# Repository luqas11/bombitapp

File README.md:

# bombitapp

### What is this
This project is a **device that controls and protects electric water pump systems**, built with an **ESP8266** based board, and operated from a mobile app developed in [React Native](https://reactnative.dev/). The device is able to preventively cut off power from the pump engines when an abnormal functioning is detected.

It's designed to operate over this preexisting pump setup:
- 2 220VAC 1/2 HP pumps.
- 2 water tanks.
- 2 water level sensors, placed inside the tanks and made by an on/off switch that turns on when the tank gets emptied and turns off when the filling process is complete. That switch operates directly at 220VAC and it's signal is plugged in to the pumps.
- 2 separated pipe circuits, each one connected to a different tank and pump. 

For different mechanical reasons, the sensors sometimes fail and keep the pumps engines running indefinitely, until manually fixed. If this happens, both the engines and the tanks could result **physically damaged** if the problem isn't solved quickly. This device's idea is to **cut pump power** if the sensor is sending the signal over a time period that exceeds some predefined threshold, to protect the setup. From a mobile app, the user can **resume the power after fixing the problem**, or **read the tank filling time history** to get an idea of the expected values. 

### Components
The project has the following components and features:

##### Hardware
- An ESP8266 based board, able to connect to the home Wi-Fi network.
- A custom PCB, to allow the ESP mounting and connection to the inputs and ouputs.
- 2 220VAC inputs, to recieve the tank water level signal. The ESP will read that signal to make it's decissions.
- 2 220VAC outputs, to power the water pumps. The ESP will power them with the water level sensor signal or not, depending on it's decissions.
- 1 5VCC input, to power the ESP board.
- 1 LED to indicate the WiFi connection status.

##### Firmware
- A sketch written in C++ and loaded to the ESP.
- Serves a webpage that allows the user to initially configure the WiFi credentials.
- Allows the level sensor signal to reach the output and power the pump until a time threshold is exceeded. After that, the connection is stopped to prevent the engine to keep working. If the signal stops before the threshold (i. e. the filling was successful), nothing happens.
- The time threshold can be setted via an HTTP request.
- Allows to resume the pump power via an HTTP request, overriding the stop state.
- The current engine working time can be get with an HTTP request.
- Allows to see the latest 10 engine run times via an HTTP request.
- Allows to see an average of all the previous engine run times via an HTTP request.
- The water level sensor status can be seen via an HTTP request (i. e. if it's on or off).

##### Mobile App
- A React Native mobile app compiled for Android.
- Gives a nice and human-friendly presentation layer for the firmware interaction, showing engine status and actions that can be made through HTTP.

### Screenshots
##### Mobile App

##### PCB 3D model

##### Circuit schematic

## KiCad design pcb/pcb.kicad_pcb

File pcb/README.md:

# PCB

This is a PCB design that implements the connections between the 220VAC relays and optocoupliers and the ESP board, along with all the necessary 3D printed parts to enable component mounting. The circuit schematic and the PCB layout are printed in the `pcb-schematic.pdf` and `pcb-layout.pdf` files respectively.

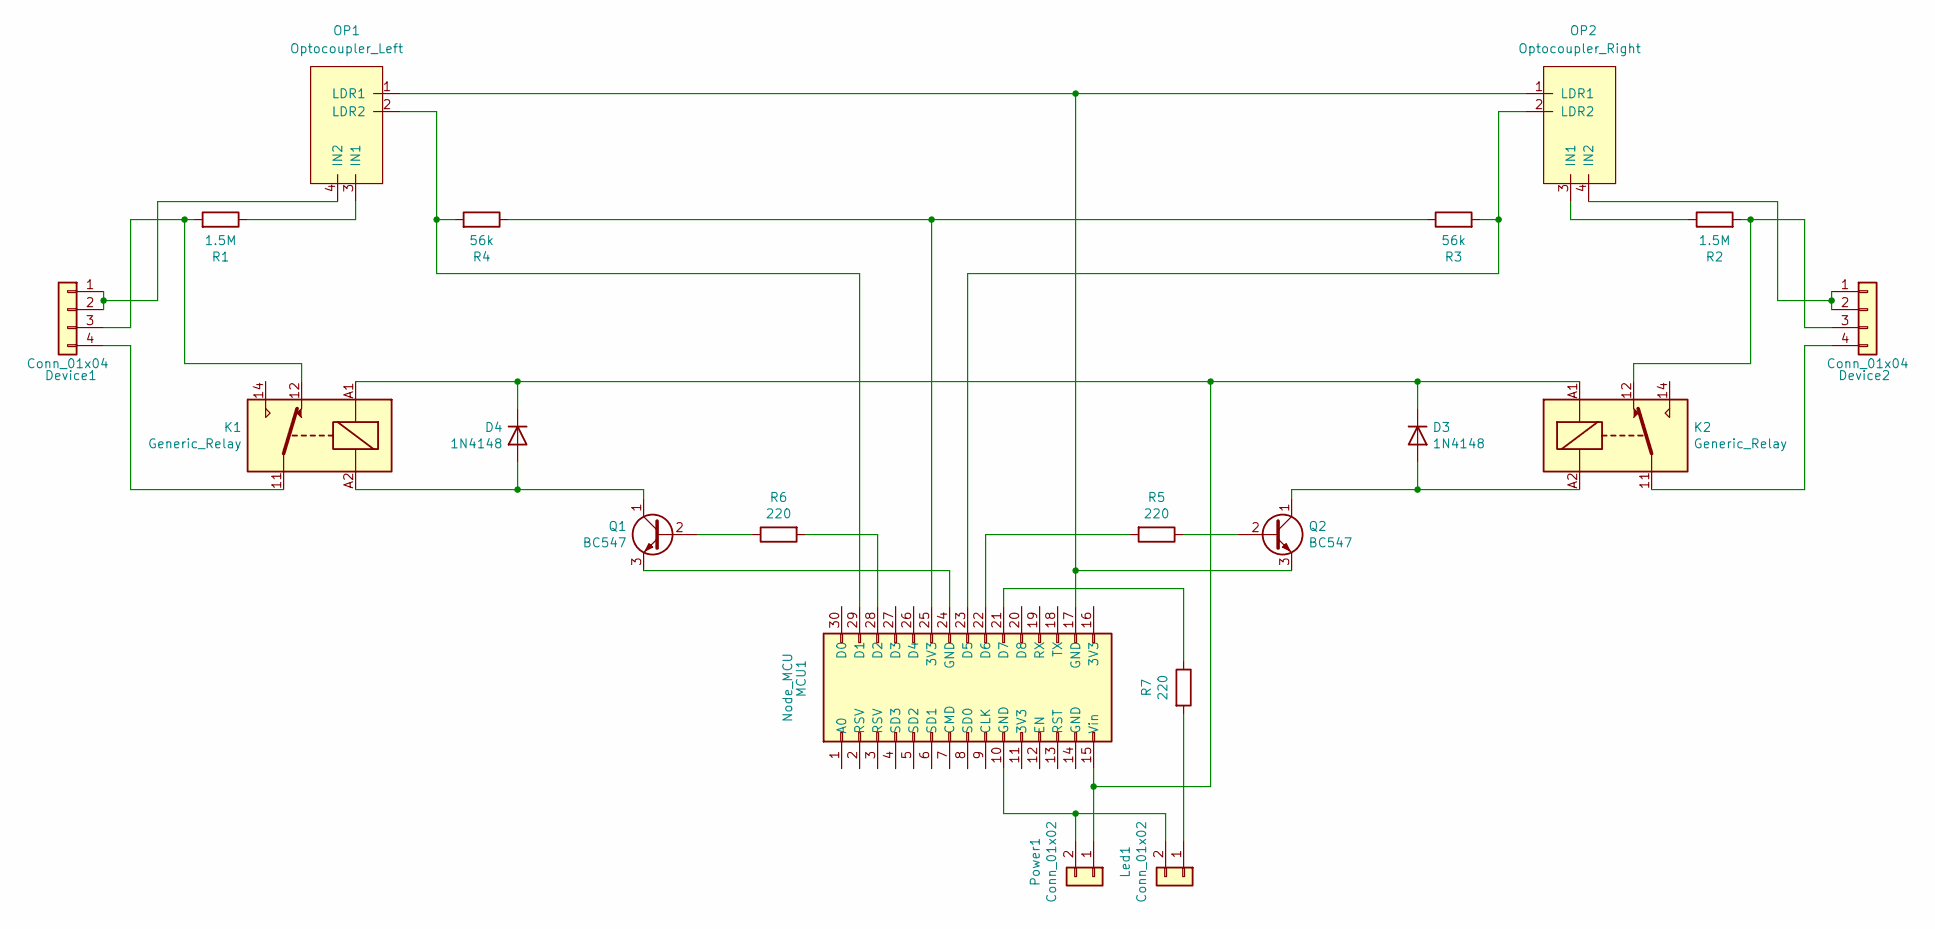
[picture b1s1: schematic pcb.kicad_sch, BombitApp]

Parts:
D3, D4: 1N4148; D_DO-35_SOD27_P7.62mm_Horizontal
Device1, Device2: Conn_01x04; TerminalBlock_1x04
K1, K2: Generic_Relay; Relay_SPDT_Finder_36.11
Led1: Conn_01x02; PinSocket_1x02
MCU1: Node_MCU
OP1: Optocoupler_Left
OP2: Optocoupler_Right
Power1: Conn_01x02; PinSocket_1x02
Q1, Q2: BC547; TO-92_Inline
R1, R2: 1.5M; R_Axial_DIN0207_L6.3mm_D2.5mm_P10.16mm_Horizontal
R3, R4: 56k; R_Axial_DIN0207_L6.3mm_D2.5mm_P10.16mm_Horizontal
R5, R6, R7: 220; R_Axial_DIN0207_L6.3mm_D2.5mm_P10.16mm_Horizontal

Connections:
unnamed: D3.2 (A), K2.A2, Q2.1 (C)
unnamed: D3.1 (K), D4.1 (K), K1.A1, K2.A1, MCU1.15 (Vin), Power1.1
unnamed: D4.2 (A), K1.A2, Q1.1 (C)
unnamed: Device1.1, Device1.2, OP1.4 (IN2)
unnamed: Device1.3, K1.12, R1.2
unnamed: Device1.4, K1.11
unnamed: Device2.1, Device2.2, OP2.4 (IN2)
unnamed: Device2.3, K2.12, R2.2
unnamed: Device2.4, K2.11
unnamed: Led1.1, R7.2
unnamed: Led1.2, MCU1.10 (GND), Power1.2
unnamed: MCU1.25 (3V3), R3.1, R4.1
unnamed: MCU1.29 (D1), OP1.2 (LDR2), R4.2
unnamed: MCU1.28 (D2), R6.2
unnamed: MCU1.23 (D5), OP2.2 (LDR2), R3.2
unnamed: MCU1.22 (D6), R5.2
unnamed: MCU1.21 (D7), R7.1
unnamed: OP1.3 (IN1), R1.1
unnamed: MCU1.17 (GND), OP1.1 (LDR1), OP2.1 (LDR1), Q2.3 (E)
unnamed: OP2.3 (IN1), R2.1
unnamed: Q1.2 (B), R6.1
unnamed: MCU1.24 (GND), Q1.3 (E)
unnamed: Q2.2 (B), R5.1

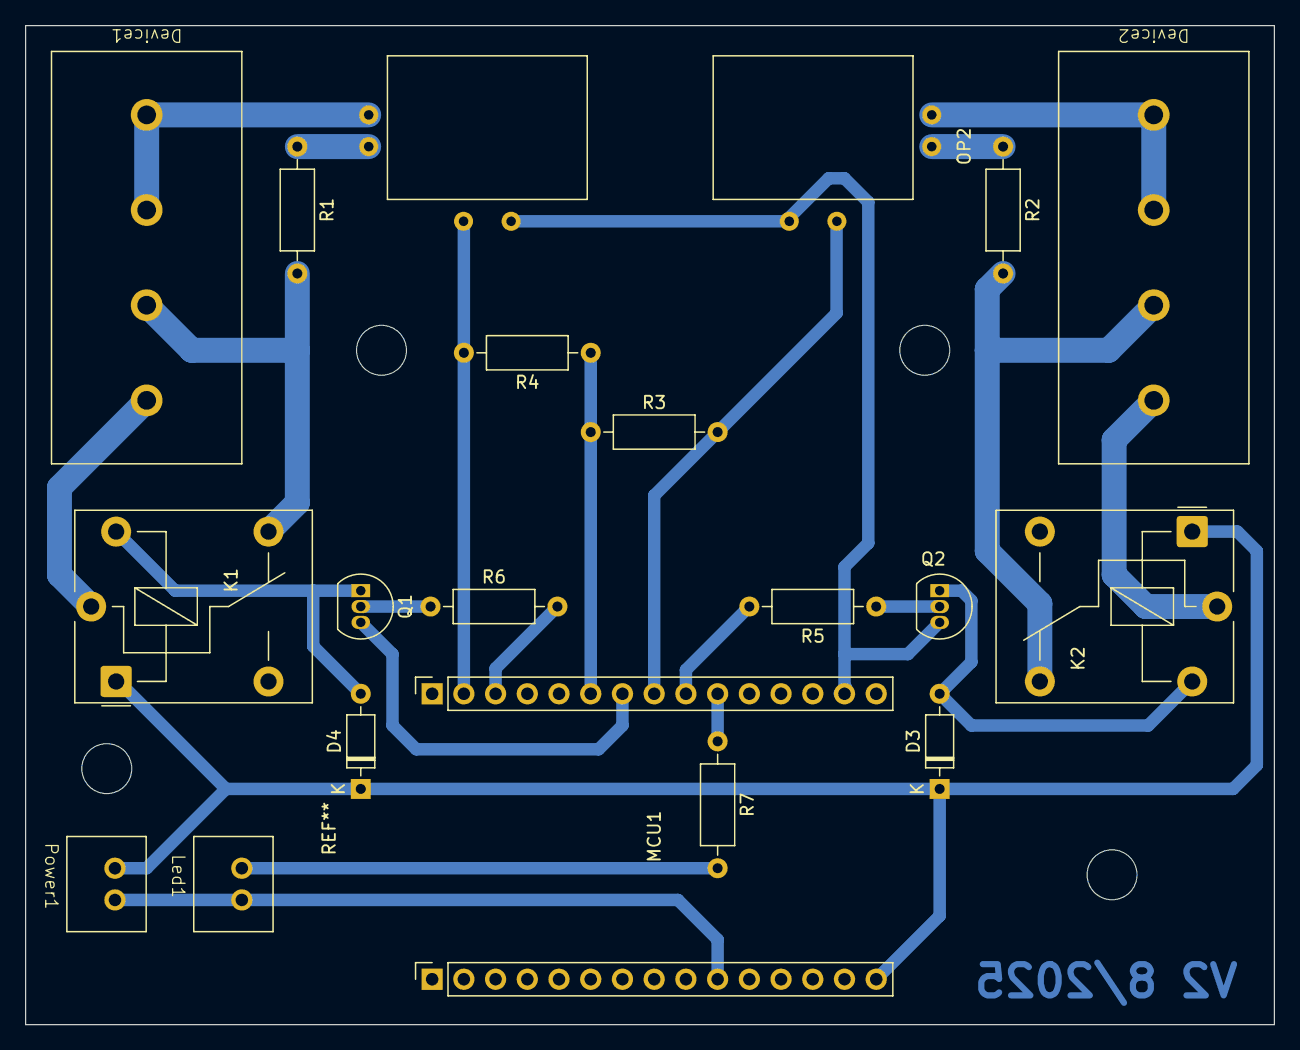
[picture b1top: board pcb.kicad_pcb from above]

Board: 2 copper layers, 100.0 x 80.0 mm, 20 parts (0 on the bottom side), 23 nets.

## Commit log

2023-05-14 Init React Native project
2023-05-14 Add postman collection
2023-05-14 Add VSCode workspace config
2023-05-14 Add json-server mock
2023-05-14 Update project version number
2023-05-14 Update Postman collection
2023-05-15 Change recommended linter
2023-05-17 Add UI desing references
2023-05-18 Add app icon and set app name
2023-05-18 Fix build error
2023-05-18 Update linter end of line configuration
2023-05-20 Add StatusCard and ButtonWithIcon components
2023-06-02 Add app navigation structure and JSDoc rules
2023-06-04 Add RequestStatusIndicator, ConfigCard, TimeLimitCard and VersionHistoryCard components and complete screens content
2023-06-04 Fix SettingsScreen visual error
2023-06-11 Add modal context and history modal implementation
2023-06-16 Add confirmation and information modals
2023-06-16 Refactor ModalContext to simplify code
2023-06-20 Add fetching logic and implement Zustand global state
2023-09-02 Relocate .vscode folder
2023-09-02 Set test context name
2023-09-02 Set context name to the correct one
2023-09-02 Configure project as a workspace
2023-09-10 Fix typo
2023-09-10 Add new sensor status indicator design
2023-09-10 Add sensor status indicator
2023-09-10 Add remaining services happy paths
2023-09-10 Add error handling to settings requests
2023-09-11 Implement name change logic to the settings screen
2023-09-11 Add loading animation design for the confirmation modal
2023-09-12 Add .env file to set environment specific variables
2023-09-12 Fix wrong time format
2023-09-12 Rename Postman files to match project name
2023-09-12 Add firmware project scaffolding
2023-09-14 Add endpoints structure and implement WiFi connection
2023-09-15 Add EEPROM management utilities
2023-09-15 Update comment
2023-09-15 Add JSON formatting utilities
2023-09-15 FIx comments format
2023-09-15 Implement Not found and status endpoints, and update Postman collection
2023-09-16 Add inputs and outputs status processing
2023-09-16 Implement history clear and limit change endpoint logic
2023-09-17 Implement input forced stop
2023-09-17 Implement EEPROM persitence to state variables
2023-09-17 Add status LED blink behaviour
2023-09-17 Fix bug reading history from memory
2023-09-17 Add LED indication for network status
2023-09-18 Remove internal pullup from inputs
2023-09-19 Refactor variable naming and update Postman collection
2023-09-19 Update comments
2023-09-19 Rename endpoint
2023-09-19 Update mock to match firmware changes
2023-09-19 Standardize variable naming across the project
2023-09-19 Update comments to match the project naming conventions
2023-09-20 Configure Android theme colors
2023-09-20 Reorder modal buttons
2023-09-20 Update files dates
2024-02-11 Add circuit and PCB design
2024-08-05 Add pcb directory to VSCode workspace
2024-08-06 Add new terminal block model and update PCB design
2024-08-08 Add pin socket model and update PCB
2024-12-20 Fix wrong output status logic
2024-12-20 Align footprints and PCB components placement
2024-12-20 Add PCB ground plane border clearance
2024-12-20 Add PCB layout and schematic PDFs
2024-12-22 Add new optocoupler model
2024-12-22 Update optocoupler footprint and PCB with new model
2024-12-22 Update schematic and layout PDFs
2024-12-23 Add power micro USB socket model
2024-12-25 Migrate firmware project from Arduino VSCode extension to IDE 2
2024-12-25 Upgrade React Native version from 0.71 to 0.76
2024-12-25 Remove RN template readme
2024-12-25 Add PCB mounting holes
2024-12-25 Add device IP setting modal design
2024-12-26 Add device IP setting modal and remove .env file IP configuration logic
2024-12-26 Update device IP setting option design
2024-12-28 Add external libraries versions to sketch
2025-01-03 Update esp8266 library version
2025-03-03 Invert cancel and accept modal buttons position
2025-03-03 Replace icon for text in HistoryModal button
2025-03-03 Revert "Invert cancel and accept modal buttons position"
    This reverts commit d99ad16db06f1a22daf244c8c2e1e73927201f67.
2025-03-03 Update design to match implemented UI
2025-03-03 Change static to dynamic IP WiFi connection
2025-04-05 Add PCB support 3D model
2025-04-06 Relocate PCB screw holes
2025-08-14 Update PCB date
2025-08-23 Update PCB support model
2025-08-23 Add power USB socket washer
2025-08-24 Add status LED case
2025-08-30 Update library version
2025-08-30 Update changelog
2025-08-30 Add README files
2025-08-30 Add example screenshots
2025-08-30 Relocate all 3D models to a folder
2026-01-18 Add WiFi configuration page
2026-01-18 Decrease WiFi connection maximum awaiting time
